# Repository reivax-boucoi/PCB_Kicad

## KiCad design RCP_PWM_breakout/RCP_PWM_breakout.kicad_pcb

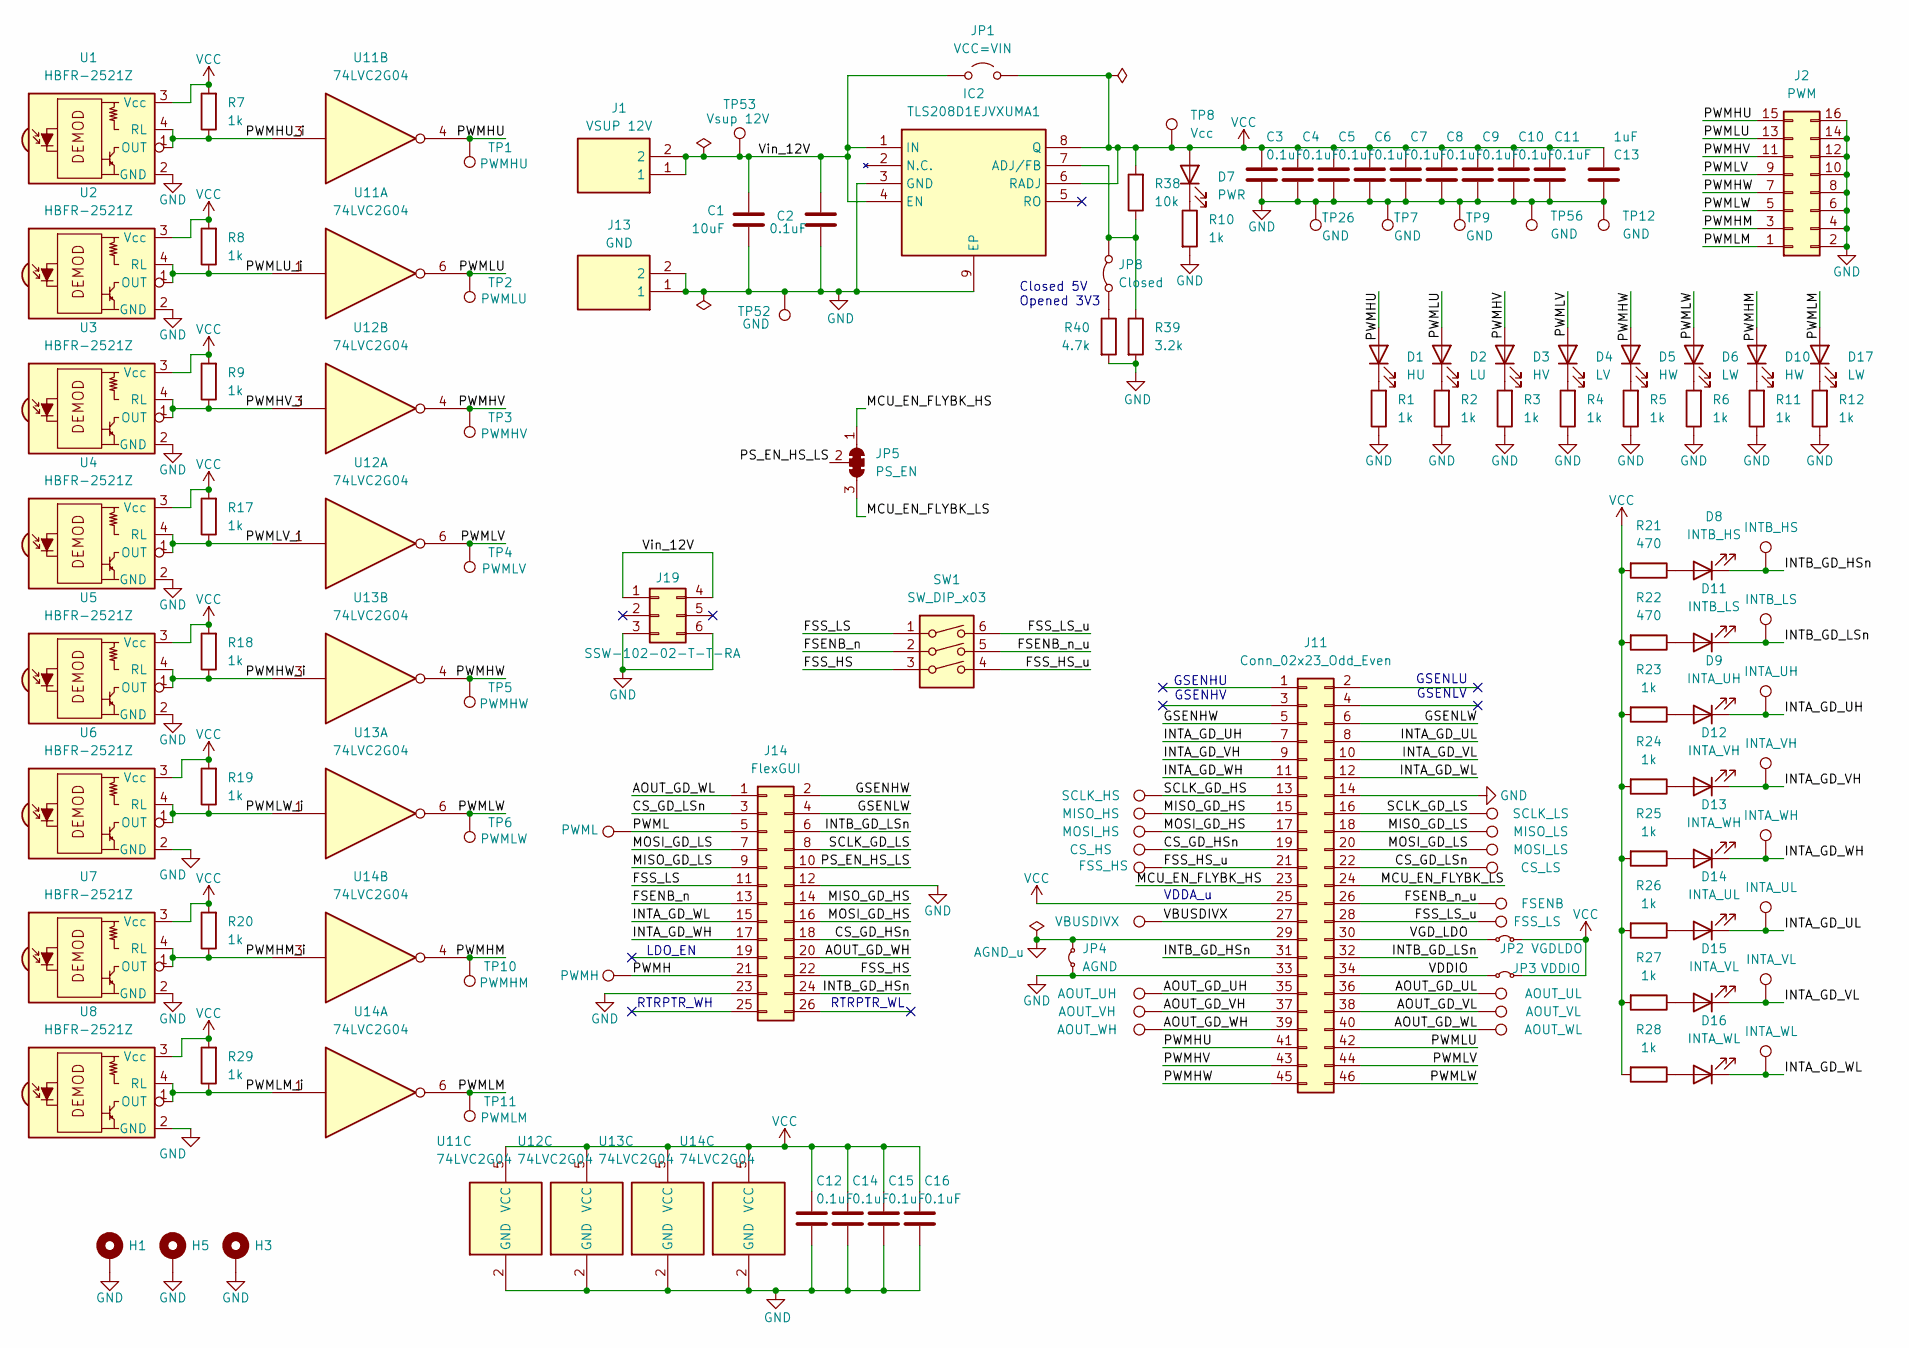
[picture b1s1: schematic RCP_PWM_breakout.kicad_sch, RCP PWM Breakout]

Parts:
C1: 10uF; C_0805_2012Metric_Pad1.18x1.45mm_HandSolder; MFG_PN 08053D106KAT2A; Mouser Part Number 581-08053D106KAT2A
C2, C3, C4, C5, C6, C7, C8, C9, C10, C11, C12, C14, C15, C16: 0.1uF; C_0603_1608Metric_Pad1.08x0.95mm_HandSolder; MFG_PN 06035C104JAT2A; Mouser Part Number 581-06035C104JAT2A
C13: 1uF; C_0805_2012Metric_Pad1.18x1.45mm_HandSolder; MFG_PN 08053D105KAT2A; Mouser Part Number 581-08053D105K
D1: HU; LED_0805_2012Metric; MFG_PN 598-8140-107F
D2: LU; LED_0805_2012Metric; MFG_PN 598-8140-107F
D3: HV; LED_0805_2012Metric; MFG_PN 598-8140-107F
D4: LV; LED_0805_2012Metric; MFG_PN 598-8140-107F
D5, D10: HW; LED_0805_2012Metric; MFG_PN 598-8140-107F
D6, D17: LW; LED_0805_2012Metric; MFG_PN 598-8140-107F
D7: PWR; LED_0805_2012Metric; MFG_PN 598-8181-107F
D8: INTB_HS; LED_0805_2012Metric; MFG_PN 598-8110-107F
D9: INTA_UH; LED_0805_2012Metric; MFG_PN 598-8130-107F
D11: INTB_LS; LED_0805_2012Metric; MFG_PN 598-8110-107F
D12: INTA_VH; LED_0805_2012Metric; MFG_PN 598-8130-107F
D13: INTA_WH; LED_0805_2012Metric; MFG_PN 598-8130-107F
D14: INTA_UL; LED_0805_2012Metric; MFG_PN 598-8130-107F
D15: INTA_VL; LED_0805_2012Metric; MFG_PN 598-8130-107F
D16: INTA_WL; LED_0805_2012Metric; MFG_PN 598-8130-107F
H1, H3, H5: MountingHole_Pad; MountingHole_3.2mm_M3_DIN965_Pad
IC2: TLS208D1EJVXUMA1; SOIC-8-1EP_3.9x4.9mm_P1.27mm_EP2.29x3mm_ThermalVias; Mouser Part Number 726-TLS208D1EJVXUMA1
J1: VSUP 12V; 1050752001; Mouser Part Number 530-105-0752-150
J2: PWM; PinHeader_2x08_P2.54mm_Vertical; MFG_PN TSW-103-07-S-D; Mouser Part Number 200-TSW10307SD
J11: Conn_02x23_Odd_Even; PinSocket_2x23_P2.54mm_Horizontal; MFG_PN SSW-123-02-T-D-RA; Mouser Part Number 200-SSW12302TDRA
J13: GND; 1050752001; Mouser Part Number 530-105-0753-150
J14: FlexGUI; PinHeader_2x13_P2.54mm_Vertical; MFG_PN TSW-113-07-S-D; Mouser Part Number 200-TSW11307SD
J19: SSW-102-02-T-T-RA; SAMTEC_SSW-102-02-T-T-RA; PARTREV R; Mouser Part Number 200-SSW10202TTRA
JP1: VCC=VIN; SolderJumper-2_P1.3mm_Open_RoundedPad1.0x1.5mm
JP2: VGDLDO; SolderJumper-2_P1.3mm_Bridged_RoundedPad1.0x1.5mm
JP3: VDDIO; SolderJumper-2_P1.3mm_Bridged_RoundedPad1.0x1.5mm
JP4: AGND; SolderJumper-2_P1.3mm_Bridged_RoundedPad1.0x1.5mm
JP5: PS_EN; SolderJumper-3_P1.3mm_Bridged123_Pad1.0x1.5mm_NumberLabels
JP8: Closed; SolderJumper-2P_Closed_THT+SMD
R1, R2, R3, R4, R5, R6, R7, R8, R9, R10, R11, R12, R17, R18, R19, R20, R23, R24, R25, R26, R27, R28, R29: 1k; R_0603_1608Metric_Pad0.98x0.95mm_HandSolder; MFG_PN CRCW06031K00FKEA; Mouser Part Number 71-CRCW0603-1.0K-E3
R21, R22: 470; R_0603_1608Metric_Pad0.98x0.95mm_HandSolder; MFG_PN CRCW0603470RFKEA; Mouser Part Number 71-CRCW0603-470-E3
R38: 10k; R_0603_1608Metric_Pad0.98x0.95mm_HandSolder; MFG_PN CRCW060310K0FKEA; Mouser Part Number 71-CRCW0603-10K-E3
R39: 3.2k; R_0603_1608Metric_Pad0.98x0.95mm_HandSolder; MFG_PN RN73H1JTTD3201F100; Mouser Part Number 660-RN73H1JT3201F100
R40: 4.7k; R_0603_1608Metric_Pad0.98x0.95mm_HandSolder; MFG_PN RK73H1JTTD4701F; Mouser Part Number 660-RK73H1JTTD4701F
SW1: SW_DIP_x03; SW_DIP_SPSTx03_Slide_6.7x9.18mm_W8.61mm_P2.54mm_LowProfile
TP1: PWMHU; TestPoint_Keystone_5012_white; MFG_PN 5012; Mouser PN 534-5012
TP2: PWMLU; TestPoint_Keystone_5012_white; MFG_PN 5012; Mouser PN 534-5012
TP3: PWMHV; TestPoint_Keystone_5012_white; MFG_PN 5012; Mouser PN 534-5012
TP4: PWMLV; TestPoint_Keystone_5012_white; MFG_PN 5012; Mouser PN 534-5012
TP5: PWMHW; TestPoint_Keystone_5012_white; MFG_PN 5012; Mouser PN 534-5012
TP6: PWMLW; TestPoint_Keystone_5012_white; MFG_PN 5012; Mouser PN 534-5012
TP7, TP9, TP26, TP52: GND; TestPoint_Keystone_5011_Black; MFG_PN 5011; Mouser PN 534-5011
TP8: Vcc; TestPoint_Keystone_5010_Red; MFG_PN 5010; Mouser PN 534-5012
TP10: PWMHM; TestPoint_Keystone_5012_white; MFG_PN 5012; Mouser PN 534-5012
TP11: PWMLM; TestPoint_Keystone_5012_white; MFG_PN 5012; Mouser PN 534-5012
TP12, TP56: GND; TestPoint_Keystone_5011_Black; MFG_PN 5011; Mouser PN 534-5012
TP18: MISO_HS; TestPoint_Keystone_5012_white; MFG_PN 5012; Mouser PN 534-5012
TP19: MOSI_HS; TestPoint_Keystone_5012_white; MFG_PN 5012; Mouser PN 534-5012
TP20: MOSI_LS; TestPoint_Keystone_5012_white; MFG_PN 5012; Mouser PN 534-5012
TP21: INTB_HS; TestPoint_Keystone_5012_white; MFG_PN 5012; Mouser PN 534-5012
TP22: AOUT_UH; TestPoint_Keystone_5012_white; MFG_PN 5012; Mouser PN 534-5012
TP23: AOUT_VH; TestPoint_Keystone_5012_white; MFG_PN 5012; Mouser PN 534-5012
TP24: AOUT_WH; TestPoint_Keystone_5012_white; MFG_PN 5012; Mouser PN 534-5012
TP25: CS_LS; TestPoint_Keystone_5012_white; MFG_PN 5012; Mouser PN 534-5012
TP27: PWMH; TestPoint_Keystone_5012_white; MFG_PN 5012; Mouser PN 534-5012
TP28: AOUT_UL; TestPoint_Keystone_5012_white; MFG_PN 5012; Mouser PN 534-5012
TP29: AOUT_VL; TestPoint_Keystone_5012_white; MFG_PN 5012; Mouser PN 534-5012
TP30: AOUT_WL; TestPoint_Keystone_5012_white; MFG_PN 5012; Mouser PN 534-5012
TP31: SCLK_HS; TestPoint_Keystone_5012_white; MFG_PN 5012; Mouser PN 534-5012
TP32: FSS_LS; TestPoint_Keystone_5012_white; MFG_PN 5012; Mouser PN 534-5012
TP33: FSENB; TestPoint_Keystone_5012_white; MFG_PN 5012; Mouser PN 534-5012
TP34: INTB_LS; TestPoint_Keystone_5012_white; MFG_PN 5012; Mouser PN 534-5012
TP35: INTA_UH; TestPoint_Keystone_5012_white; MFG_PN 5012; Mouser PN 534-5012
TP36: INTA_VH; TestPoint_Keystone_5012_white; MFG_PN 5012; Mouser PN 534-5012
TP37: INTA_WH; TestPoint_Keystone_5012_white; MFG_PN 5012; Mouser PN 534-5012
TP38: INTA_UL; TestPoint_Keystone_5012_white; MFG_PN 5012; Mouser PN 534-5012
TP39: INTA_VL; TestPoint_Keystone_5012_white; MFG_PN 5012; Mouser PN 534-5012
TP40: INTA_WL; TestPoint_Keystone_5012_white; MFG_PN 5012; Mouser PN 534-5012
TP41: FSS_HS; TestPoint_Keystone_5012_white; MFG_PN 5012; Mouser PN 534-5012
TP42: SCLK_LS; TestPoint_Keystone_5012_white; MFG_PN 5012; Mouser PN 534-5012
TP53: Vsup 12V; TestPoint_Keystone_5010_Red; MFG_PN 5010; Mouser PN 534-5012
TP54: PWML; TestPoint_Keystone_5012_white; MFG_PN 5012; Mouser PN 534-5012
TP60: CS_HS; TestPoint_Keystone_5012_white; MFG_PN 5012; Mouser PN 534-5012
TP61: MISO_LS; TestPoint_Keystone_5012_white; MFG_PN 5012; Mouser PN 534-5012
TP62: VBUSDIVX; TestPoint_Keystone_5012_white; MFG_PN 5012; Mouser PN 534-5012
U1, U2, U3, U4, U5, U6, U7, U8: HBFR-2521Z; FR50MHNR
U11, U12, U13, U14: 74LVC2G04; SOT-23-6_Handsoldering

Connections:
/AOUT_GD_UH: J11.35, TP22.1 (1_1)
/AOUT_GD_UL: J11.36, TP28.1 (1_1)
/AOUT_GD_VH: J11.37, TP23.1 (1_1)
/AOUT_GD_VL: J11.38, TP29.1 (1_1)
/AOUT_GD_WH: J11.39, J14.20, TP24.1 (1_1)
/AOUT_GD_WL: J11.40, J14.1, TP30.1 (1_1)
/CS_GD_HSn: J11.19, J14.18, TP60.1 (1_1)
/CS_GD_LSn: J11.22, J14.3, TP25.1 (1_1)
/FSENB_n: J14.13, SW1.2
/FSENB_n_u: J11.26, SW1.5, TP33.1 (1_1)
/FSS_HS: J14.22, SW1.3
/FSS_HS_u: J11.21, SW1.4, TP41.1 (1_1)
/FSS_LS: J14.11, SW1.1
/FSS_LS_u: J11.28, SW1.6, TP32.1 (1_1)
/GSENHW: J11.5, J14.2
/GSENLW: J11.6, J14.4
/INTA_GD_UH: D9.1 (K), J11.7, TP35.1 (1_1)
/INTA_GD_UL: D14.1 (K), J11.8, TP38.1 (1_1)
/INTA_GD_VH: D12.1 (K), J11.9, TP36.1 (1_1)
/INTA_GD_VL: D15.1 (K), J11.10, TP39.1 (1_1)
/INTA_GD_WH: D13.1 (K), J11.11, J14.17, TP37.1 (1_1)
/INTA_GD_WL: D16.1 (K), J11.12, J14.15, TP40.1 (1_1)
/INTB_GD_HSn: D8.1 (K), J11.31, J14.24, TP21.1 (1_1)
/INTB_GD_LSn: D11.1 (K), J11.32, J14.6, TP34.1 (1_1)
/MCU_EN_FLYBK_HS: J11.23, JP5.1 (A)
/MCU_EN_FLYBK_LS: J11.24, JP5.3 (B)
/MISO_GD_HS: J11.15, J14.14, TP18.1 (1_1)
/MISO_GD_LS: J11.18, J14.9, TP61.1 (1_1)
/MOSI_GD_HS: J11.17, J14.16, TP19.1 (1_1)
/MOSI_GD_LS: J11.20, J14.7, TP20.1 (1_1)
/PS_EN_HS_LS: J14.10, JP5.2 (C)
/PWMH: J14.21, TP27.1 (1_1)
/PWMHM: D10.2 (A), J2.3, TP10.1 (1_1), U14.4
/PWMHM_i: R20.1, U7.1 (OUT), U7.4 (RL), U14.3
/PWMHU: D1.2 (A), J2.15, J11.41, TP1.1 (1_1), U11.4
/PWMHU_i: R7.1, U1.1 (OUT), U1.4 (RL), U11.3
/PWMHV: D3.2 (A), J2.11, J11.43, TP3.1 (1_1), U12.4
/PWMHV_i: R9.1, U3.1 (OUT), U3.4 (RL), U12.3
/PWMHW: D5.2 (A), J2.7, J11.45, TP5.1 (1_1), U13.4
/PWMHW_i: R18.1, U5.1 (OUT), U5.4 (RL), U13.3
/PWML: J14.5, TP54.1 (1_1)
/PWMLM: D17.2 (A), J2.1, TP11.1 (1_1), U14.6
/PWMLM_i: R29.1, U8.1 (OUT), U8.4 (RL), U14.1
/PWMLU: D2.2 (A), J2.13, J11.42, TP2.1 (1_1), U11.6
/PWMLU_i: R8.1, U2.1 (OUT), U2.4 (RL), U11.1
/PWMLV: D4.2 (A), J2.9, J11.44, TP4.1 (1_1), U12.6
/PWMLV_i: R17.1, U4.1 (OUT), U4.4 (RL), U12.1
/PWMLW: D6.2 (A), J2.5, J11.46, TP6.1 (1_1), U13.6
/PWMLW_i: R19.1, U6.1 (OUT), U6.4 (RL), U13.1
/SCLK_GD_HS: J11.13, TP31.1 (1_1)
/SCLK_GD_LS: J11.16, J14.8, TP42.1 (1_1)
/VBUSDIVX: J11.27, TP62.1 (1_1)
/VDDIO: J11.34, JP3.1 (A)
/VGD_LDO: J11.30, JP2.1 (A)
/Vin_12V: C1.1, C2.2, IC2.1 (IN), IC2.4 (EN), J1.1, J1.2, J19.1, J19.4, JP1.1 (A), TP53.1 (1_1)
AGND_u: J11.29, JP4.2 (B)
GND: C1.2, C2.1, C3.2, C4.2, C5.2, C6.2, C7.2, C8.2, C9.2, C10.2, C11.2, C12.2, C13.1, C14.2, C15.2, C16.2, H1.1 (1_1), H3.1 (1_1), H5.1 (1_1), IC2.3 (GND), IC2.9 (EP), J2.2, J2.4, J2.6, J2.8, J2.10, J2.12, J2.14, J2.16, J11.14, J11.33, J13.1, J13.2, J14.12, J14.23, J19.3, J19.6, JP4.1 (A), R1.1, R2.1, R3.1, R4.1, R5.1, R6.1, R10.2, R11.1, R12.1, R39.2, R40.2, TP7.1 (1_1), TP9.1 (1_1), TP12.1 (1_1), TP26.1 (1_1), TP52.1 (1_1), TP56.1 (1_1), U1.2 (GND), U1.5 (GND), U1.8 (GND), U2.2 (GND), U2.5 (GND), U2.8 (GND), U3.2 (GND), U3.5 (GND), U3.8 (GND), U4.2 (GND), U4.5 (GND), U4.8 (GND), U5.2 (GND), U5.5 (GND), U5.8 (GND), U6.2 (GND), U6.5 (GND), U6.8 (GND), U7.2 (GND), U7.5 (GND), U7.8 (GND), U8.2 (GND), U8.5 (GND), U8.8 (GND), U11.2 (GND), U12.2 (GND), U13.2 (GND), U14.2 (GND)
unnamed: D1.1 (K), R1.2
unnamed: D2.1 (K), R2.2
unnamed: D3.1 (K), R3.2
unnamed: D4.1 (K), R4.2
unnamed: D5.1 (K), R5.2
unnamed: D6.1 (K), R6.2
unnamed: D7.1 (K), R10.1
unnamed: D8.2 (A), R21.1
unnamed: D9.2 (A), R23.1
unnamed: D10.1 (K), R11.2
unnamed: D11.2 (A), R22.1
unnamed: D12.2 (A), R24.1
unnamed: D13.2 (A), R25.1
unnamed: D14.2 (A), R26.1
unnamed: D15.2 (A), R27.1
unnamed: D16.2 (A), R28.1
unnamed: D17.1 (K), R12.2
unnamed: IC2.7 (ADJ/FB), JP8.2 (B), R38.1, R39.1
unnamed: JP8.1 (A), R40.1
VCC: C3.1, C4.1, C5.1, C6.1, C7.1, C8.1, C9.1, C10.1, C11.1, C12.1, C13.2, C14.1, C15.1, C16.1, D7.2 (A), IC2.6 (RADJ), IC2.8 (Q), J11.25, JP1.2 (B), JP2.2 (B), JP3.2 (B), R7.2, R8.2, R9.2, R17.2, R18.2, R19.2, R20.2, R21.2, R22.2, R23.2, R24.2, R25.2, R26.2, R27.2, R28.2, R29.2, R38.2, TP8.1 (1_1), U1.3 (Vcc), U2.3 (Vcc), U3.3 (Vcc), U4.3 (Vcc), U5.3 (Vcc), U6.3 (Vcc), U7.3 (Vcc), U8.3 (Vcc), U11.5 (VCC), U12.5 (VCC), U13.5 (VCC), U14.5 (VCC)

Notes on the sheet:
RTRPTR_WH
LDO_EN
RTRPTR_WL
VDDA_u
GSENLU GSENLV
Closed 5V Opened 3V3
GSENHU GSENHV

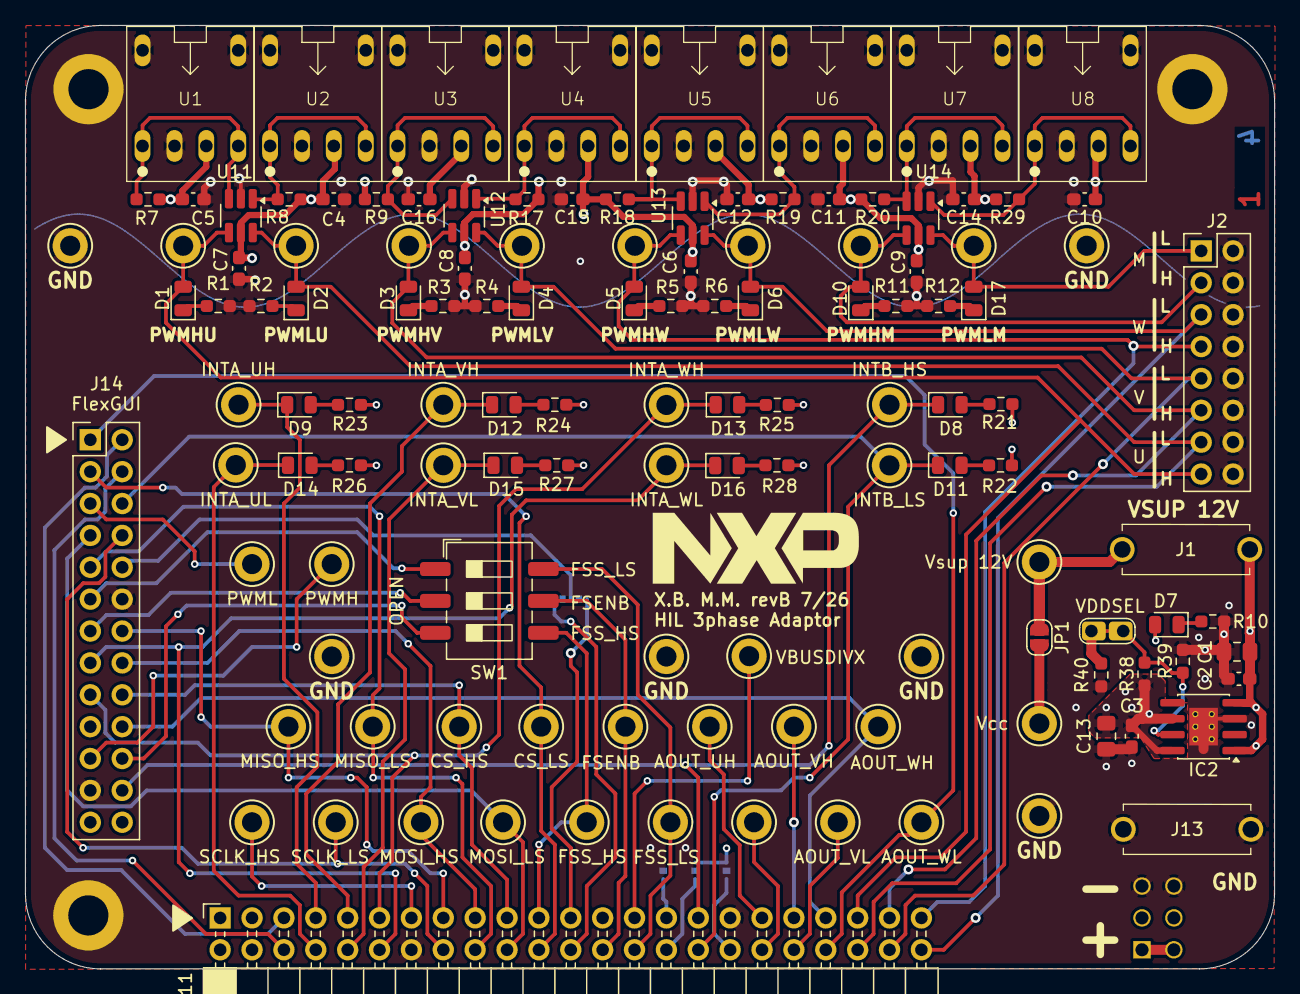
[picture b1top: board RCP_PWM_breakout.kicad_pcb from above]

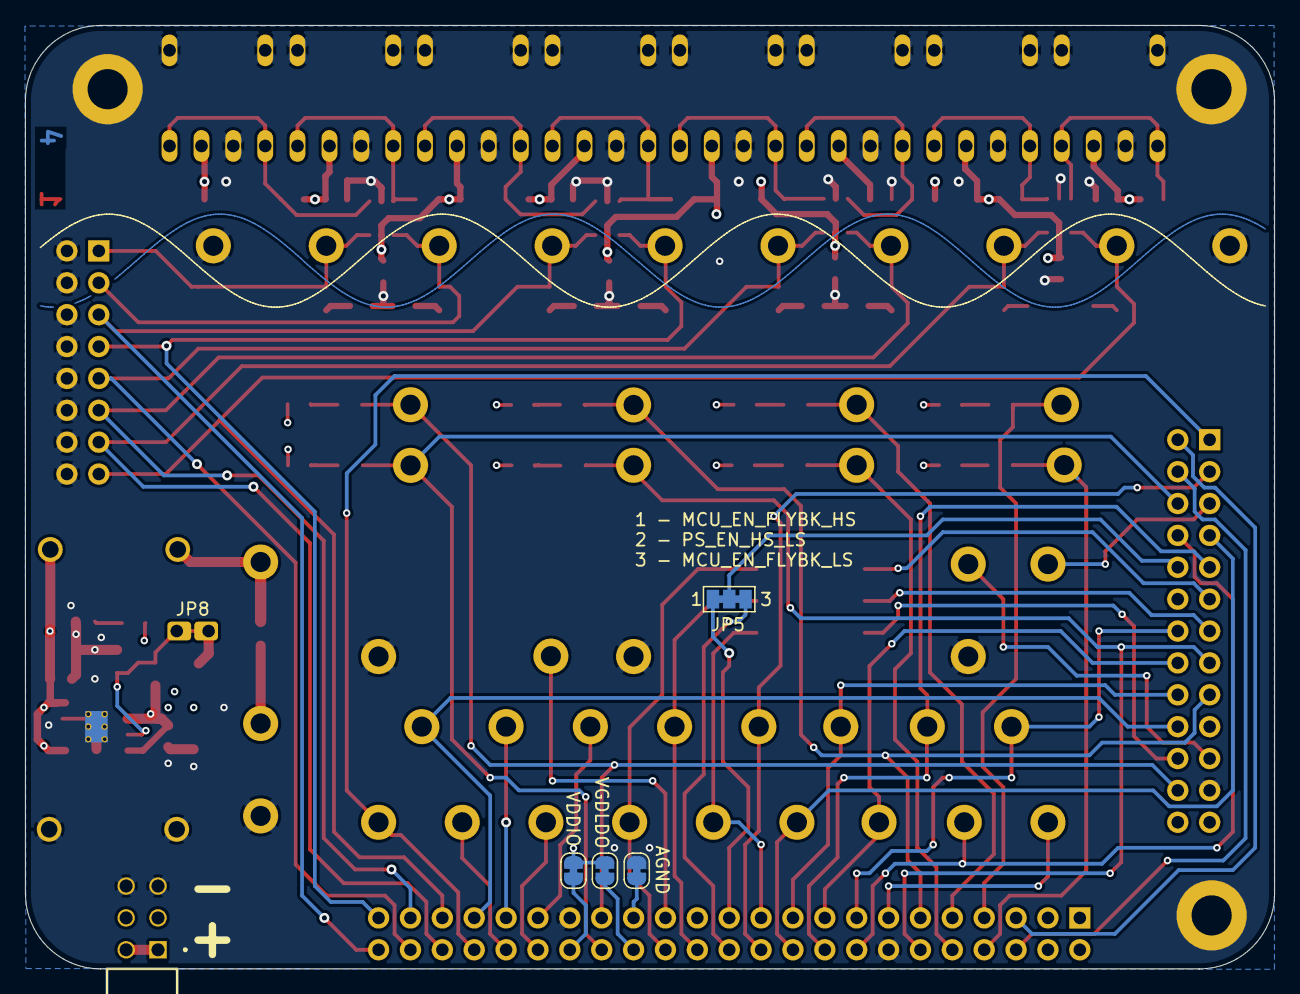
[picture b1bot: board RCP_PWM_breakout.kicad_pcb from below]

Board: 4 copper layers, 99.5 x 75.2 mm, 134 parts (5 on the bottom side), 77 nets.

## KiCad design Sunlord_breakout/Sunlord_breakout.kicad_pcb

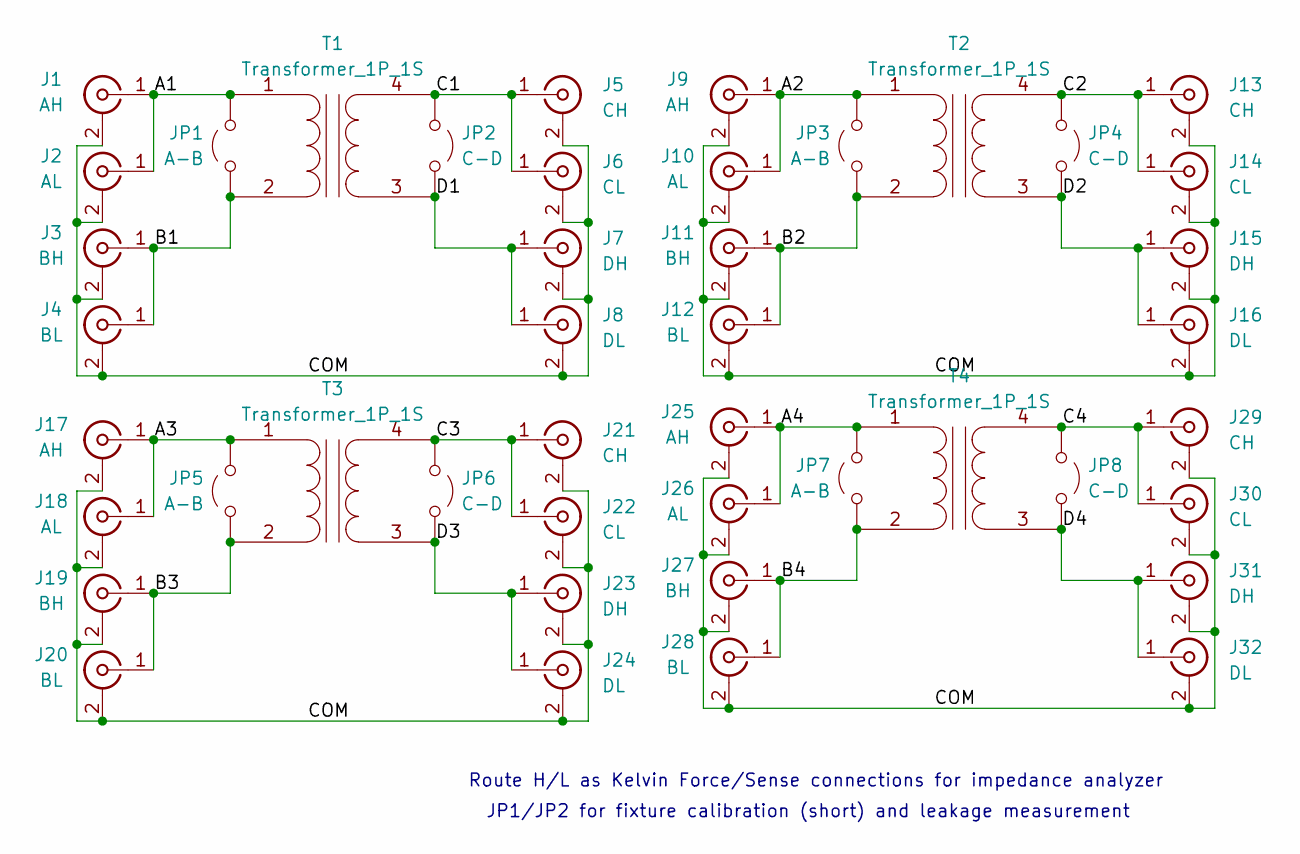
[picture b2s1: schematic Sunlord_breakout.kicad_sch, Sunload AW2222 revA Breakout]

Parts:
J1, J9, J17, J25: AH; SMA_Samtec_SMA-J-P-H-ST-EM1_EdgeMount
J2, J10, J18, J26: AL; SMA_Samtec_SMA-J-P-H-ST-EM1_EdgeMount
J3, J11, J19, J27: BH; SMA_Samtec_SMA-J-P-H-ST-EM1_EdgeMount
J4, J12, J20, J28: BL; SMA_Samtec_SMA-J-P-H-ST-EM1_EdgeMount
J5, J13, J21, J29: CH; SMA_Samtec_SMA-J-P-H-ST-EM1_EdgeMount
J6, J14, J22, J30: CL; SMA_Samtec_SMA-J-P-H-ST-EM1_EdgeMount
J7, J15, J23, J31: DH; SMA_Samtec_SMA-J-P-H-ST-EM1_EdgeMount
J8, J16, J24, J32: DL; SMA_Samtec_SMA-J-P-H-ST-EM1_EdgeMount
JP1, JP3, JP5, JP7: A-B; SolderJumper-2_P1.3mm_Open_RoundedPad1.0x1.5mm
JP2, JP4, JP6, JP8: C-D; SolderJumper-2_P1.3mm_Open_RoundedPad1.0x1.5mm
T1, T2, T3, T4: Transformer_1P_1S; AW2222_Sunlord_µXFMR

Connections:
/A1: J1.1 (In), J2.1 (In), JP1.2 (B), T1.1 (AA)
/A2: J9.1 (In), J10.1 (In), JP3.2 (B), T2.1 (AA)
/A3: J17.1 (In), J18.1 (In), JP5.2 (B), T3.1 (AA)
/A4: J25.1 (In), J26.1 (In), JP7.2 (B), T4.1 (AA)
/B1: J3.1 (In), J4.1 (In), JP1.1 (A), T1.2 (AB)
/B2: J11.1 (In), J12.1 (In), JP3.1 (A), T2.2 (AB)
/B3: J19.1 (In), J20.1 (In), JP5.1 (A), T3.2 (AB)
/B4: J27.1 (In), J28.1 (In), JP7.1 (A), T4.2 (AB)
/C1: J5.1 (In), J6.1 (In), JP2.1 (A), T1.4 (SB)
/C2: J13.1 (In), J14.1 (In), JP4.1 (A), T2.4 (SB)
/C3: J21.1 (In), J22.1 (In), JP6.1 (A), T3.4 (SB)
/C4: J29.1 (In), J30.1 (In), JP8.1 (A), T4.4 (SB)
/COM: J1.2 (Ext), J2.2 (Ext), J3.2 (Ext), J4.2 (Ext), J5.2 (Ext), J6.2 (Ext), J7.2 (Ext), J8.2 (Ext), J9.2 (Ext), J10.2 (Ext), J11.2 (Ext), J12.2 (Ext), J13.2 (Ext), J14.2 (Ext), J15.2 (Ext), J16.2 (Ext), J17.2 (Ext), J18.2 (Ext), J19.2 (Ext), J20.2 (Ext), J21.2 (Ext), J22.2 (Ext), J23.2 (Ext), J24.2 (Ext), J25.2 (Ext), J26.2 (Ext), J27.2 (Ext), J28.2 (Ext), J29.2 (Ext), J30.2 (Ext), J31.2 (Ext), J32.2 (Ext)
/D1: J7.1 (In), J8.1 (In), JP2.2 (B), T1.3 (SA)
/D2: J15.1 (In), J16.1 (In), JP4.2 (B), T2.3 (SA)
/D3: J23.1 (In), J24.1 (In), JP6.2 (B), T3.3 (SA)
/D4: J31.1 (In), J32.1 (In), JP8.2 (B), T4.3 (SA)

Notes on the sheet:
JP1/JP2 for fixture calibration (short) and leakage measurement
Route H/L as Kelvin Force/Sense connections for impedance analyzer

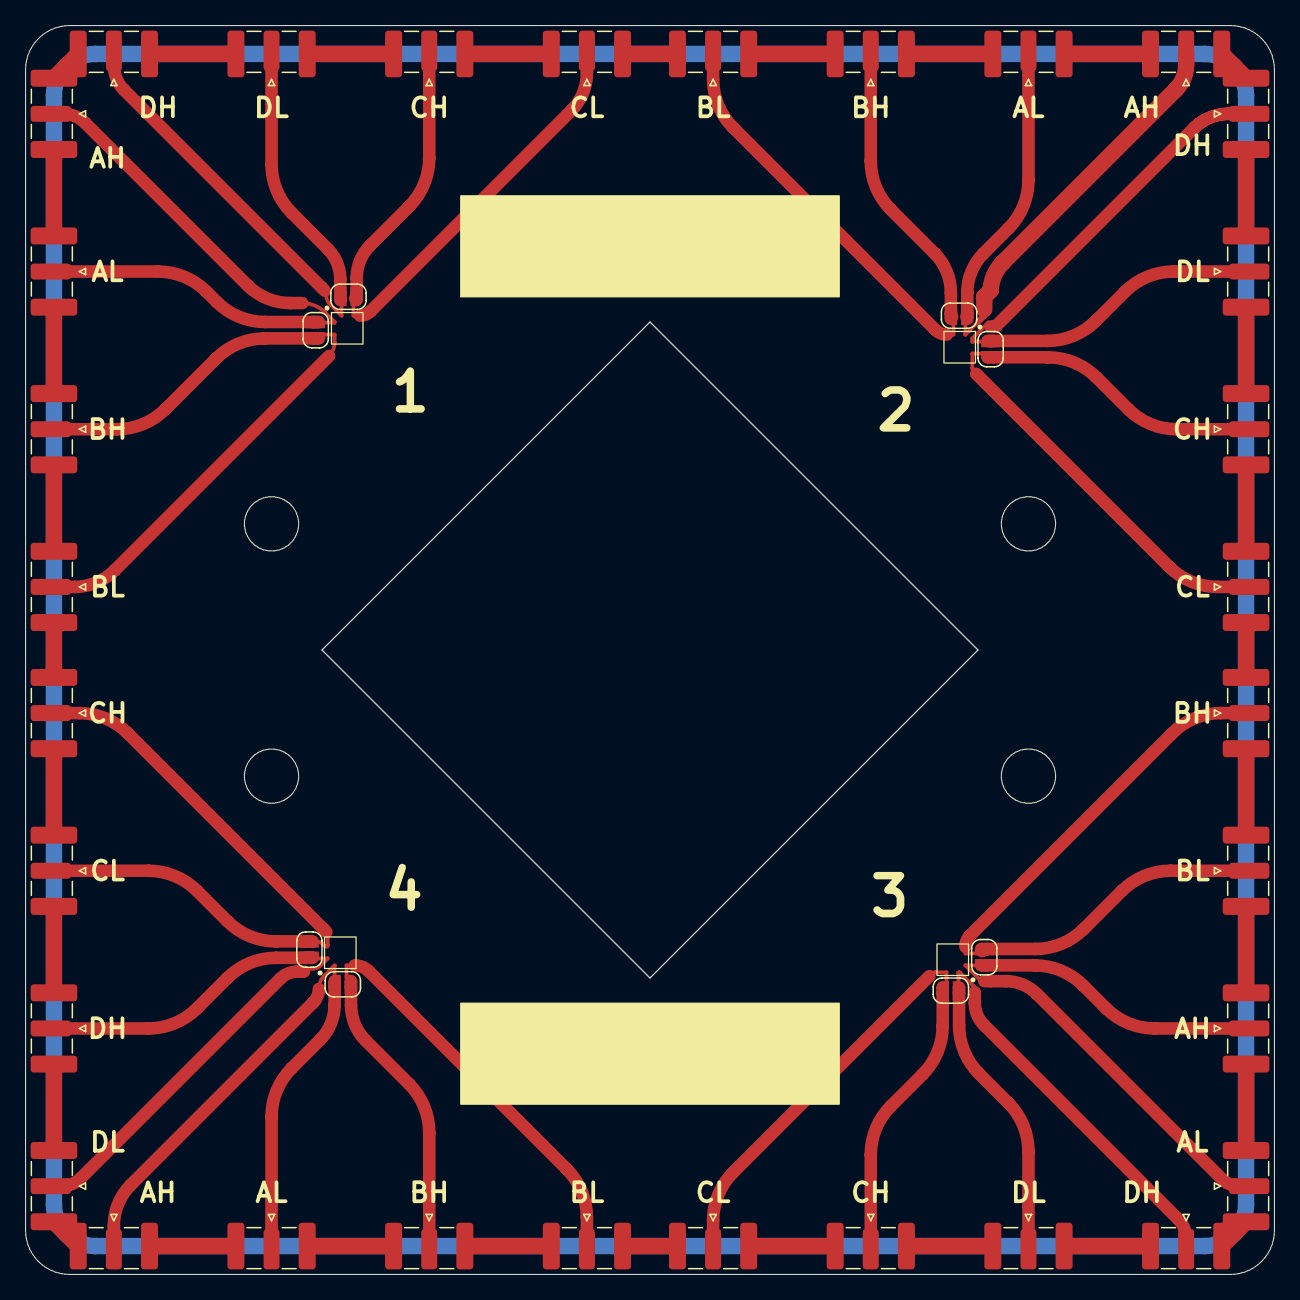
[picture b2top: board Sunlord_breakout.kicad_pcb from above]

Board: 2 copper layers, 99.0 x 99.0 mm, 44 parts (0 on the bottom side), 17 nets.

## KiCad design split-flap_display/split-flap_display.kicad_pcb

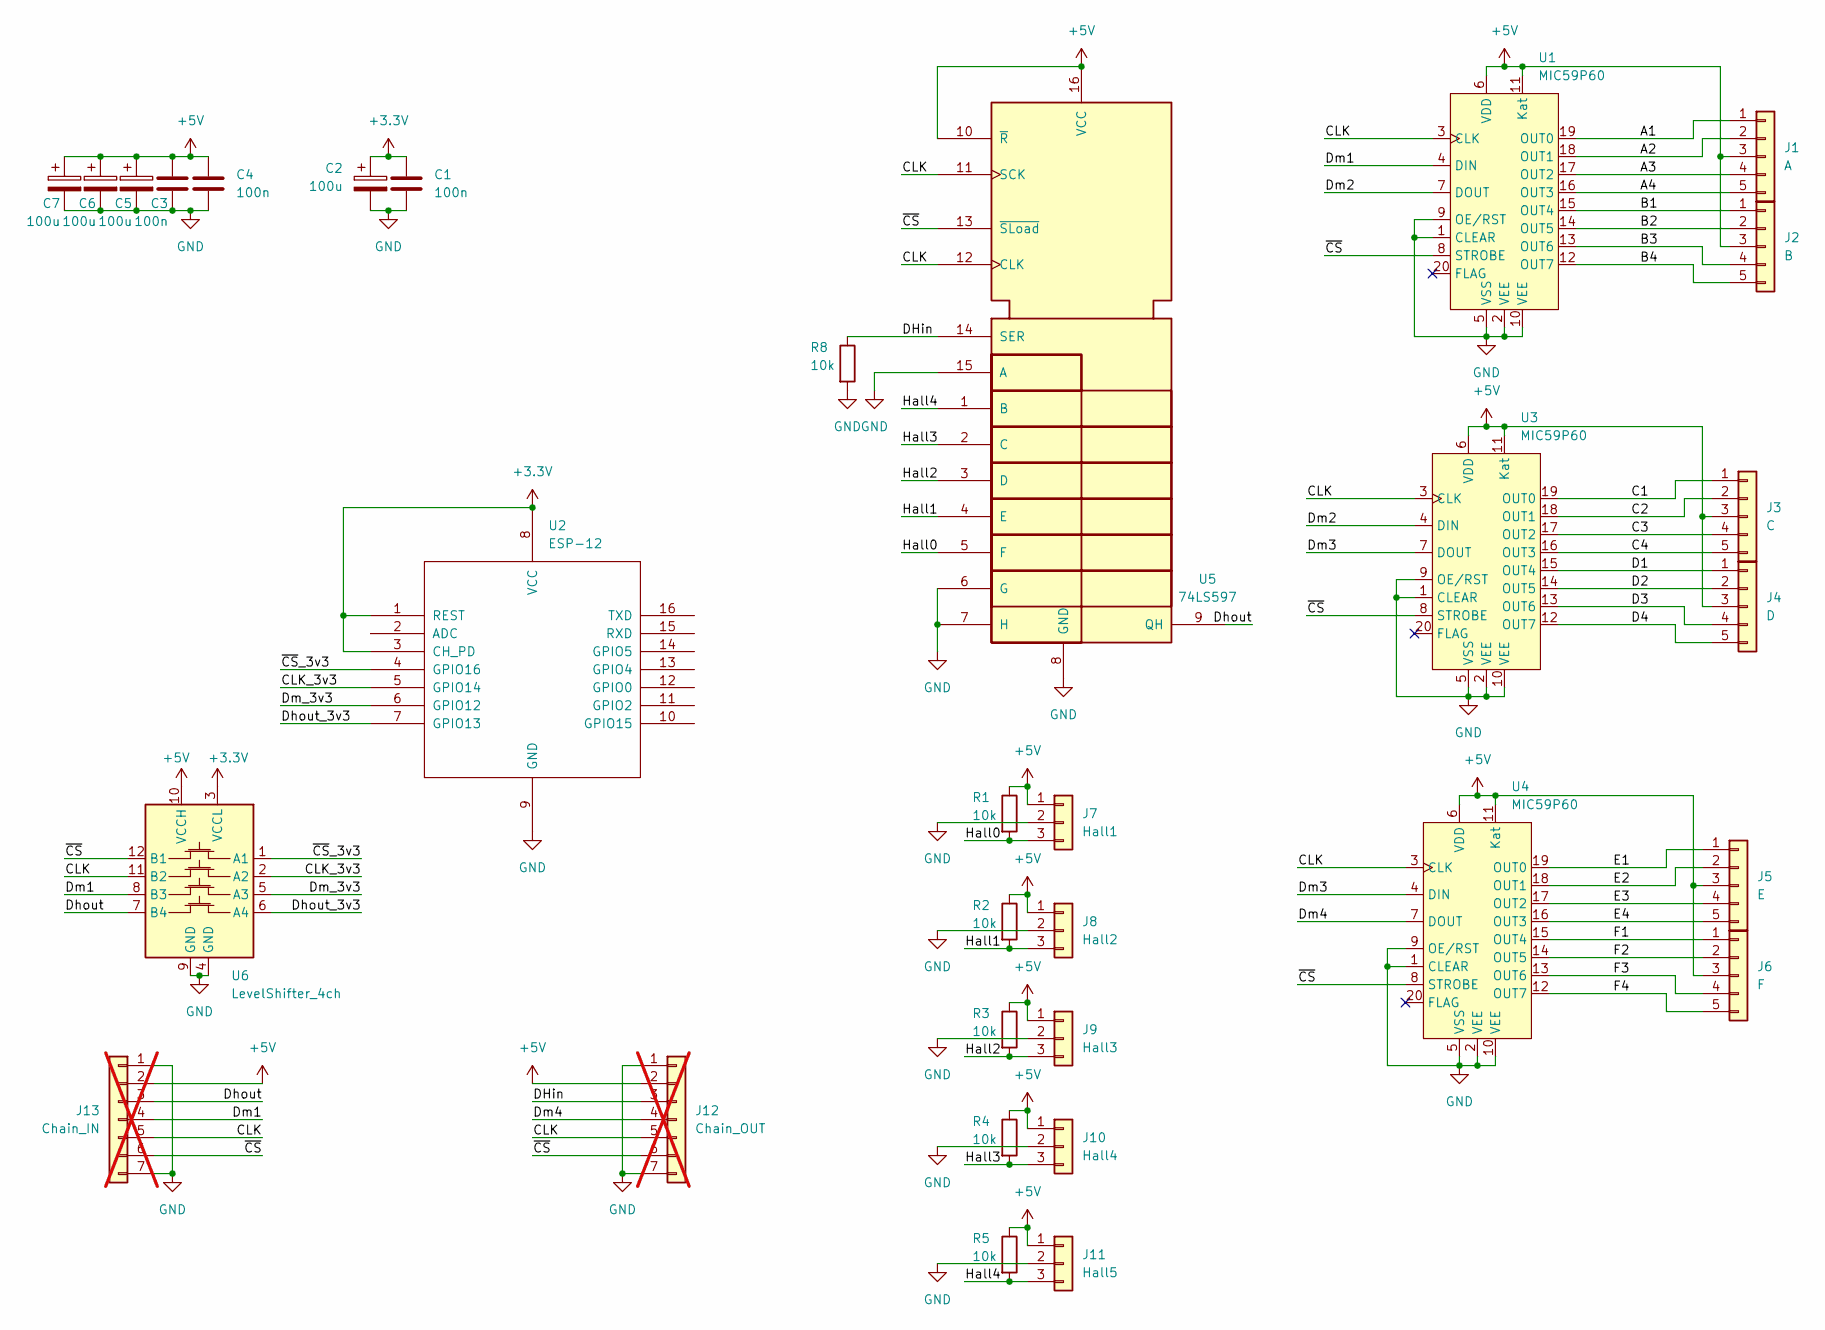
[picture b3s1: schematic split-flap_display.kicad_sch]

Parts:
C1, C3, C4: 100n; C_Disc_D6.0mm_W2.5mm_P5.00mm
C2, C5, C6, C7: 100u; CP_Radial_D8.0mm_P5.00mm
J1: A; PinHeader_1x05_P2.54mm_Vertical
J2: B; PinHeader_1x05_P2.54mm_Vertical
J3: C; PinHeader_1x05_P2.54mm_Vertical
J4: D; PinHeader_1x05_P2.54mm_Vertical
J5: E; PinHeader_1x05_P2.54mm_Vertical
J6: F; PinHeader_1x05_P2.54mm_Vertical
J7: Hall1; PinHeader_1x03_P2.54mm_Vertical
J8: Hall2; PinHeader_1x03_P2.54mm_Vertical
J9: Hall3; PinHeader_1x03_P2.54mm_Vertical
J10: Hall4; PinHeader_1x03_P2.54mm_Vertical
J11: Hall5; PinHeader_1x03_P2.54mm_Vertical
J12: Chain_OUT; PinHeader_1x07_P2.54mm_Vertical; not fitted
J13: Chain_IN; PinHeader_1x07_P2.54mm_Vertical; not fitted
R1, R2, R3, R4, R5: 10k; R_Axial_DIN0207_L6.3mm_D2.5mm_P5.08mm_Vertical
R8: 10k; R_Axial_DIN0207_L6.3mm_D2.5mm_P2.54mm_Vertical
U1, U3, U4: MIC59P60; DIP-20_W7.62mm_LongPads
U2: ESP-12
U5: 74LS597; DIP-16_W7.62mm_LongPads
U6: LevelShifter_4ch; DIP-12_LevelShifter

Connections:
+3.3V: C1.1, C2.1, U2.1 (REST), U2.3 (CH_PD), U2.8 (VCC), U6.3 (VCCL)
+5V: C3.1, C4.1, C5.1, C6.1, C7.1, J1.3, J2.3, J3.3, J4.3, J5.3, J6.3, J7.1, J8.1, J9.1, J10.1, J11.1, J12.2, J13.2, R1.1, R2.1, R3.1, R4.1, R5.1, U1.6 (VDD), U1.11 (Kat), U3.6 (VDD), U3.11 (Kat), U4.6 (VDD), U4.11 (Kat), U5.10 (~R), U5.16 (VCC), U6.10 (VCCH)
/A1: J1.1, U1.19 (OUT0)
/A2: J1.2, U1.18 (OUT1)
/A3: J1.4, U1.17 (OUT2)
/A4: J1.5, U1.16 (OUT3)
/B1: J2.1, U1.15 (OUT4)
/B2: J2.2, U1.14 (OUT5)
/B3: J2.4, U1.13 (OUT6)
/B4: J2.5, U1.12 (OUT7)
/C1: J3.1, U3.19 (OUT0)
/C2: J3.2, U3.18 (OUT1)
/C3: J3.4, U3.17 (OUT2)
/C4: J3.5, U3.16 (OUT3)
/CLK: J12.5, J13.5, U1.3 (CLK), U3.3 (CLK), U4.3 (CLK), U5.11 (SCK), U5.12 (CLK), U6.11 (B2)
/CLK_3v3: U2.5 (GPIO14), U6.2 (A2)
/D1: J4.1, U3.15 (OUT4)
/D2: J4.2, U3.14 (OUT5)
/D3: J4.4, U3.13 (OUT6)
/D4: J4.5, U3.12 (OUT7)
/DHin: J12.3, R8.1, U5.14 (SER)
/Dhout: J13.3, U5.9 (QH), U6.7 (B4)
/Dhout_3v3: U2.7 (GPIO13), U6.6 (A4)
/Dm1: J13.4, U1.4 (DIN), U6.8 (B3)
/Dm2: U1.7 (DOUT), U3.4 (DIN)
/Dm3: U3.7 (DOUT), U4.4 (DIN)
/Dm4: J12.4, U4.7 (DOUT)
/Dm_3v3: U2.6 (GPIO12), U6.5 (A3)
/E1: J5.1, U4.19 (OUT0)
/E2: J5.2, U4.18 (OUT1)
/E3: J5.4, U4.17 (OUT2)
/E4: J5.5, U4.16 (OUT3)
/F1: J6.1, U4.15 (OUT4)
/F2: J6.2, U4.14 (OUT5)
/F3: J6.4, U4.13 (OUT6)
/F4: J6.5, U4.12 (OUT7)
/Hall0: J7.3, R1.2, U5.5 (F)
/Hall1: J8.3, R2.2, U5.4 (E)
/Hall2: J9.3, R3.2, U5.3 (D)
/Hall3: J10.3, R4.2, U5.2 (C)
/Hall4: J11.3, R5.2, U5.1 (B)
/~CS: J12.6, J13.6, U1.8 (STROBE), U3.8 (STROBE), U4.8 (STROBE), U5.13 (~SLoad), U6.12 (B1)
/~CS_3v3: U2.4 (GPIO16), U6.1 (A1)
GND: C1.2, C2.2, C3.2, C4.2, C5.2, C6.2, C7.2, J7.2, J8.2, J9.2, J10.2, J11.2, J12.1, J12.7, J13.1, J13.7, R8.2, U1.1 (CLEAR), U1.2 (VEE), U1.5 (VSS), U1.9 (OE/RST), U1.10 (VEE), U2.9 (GND), U3.1 (CLEAR), U3.2 (VEE), U3.5 (VSS), U3.9 (OE/RST), U3.10 (VEE), U4.1 (CLEAR), U4.2 (VEE), U4.5 (VSS), U4.9 (OE/RST), U4.10 (VEE), U5.6 (G), U5.7 (H), U5.8 (GND), U5.15 (A), U6.4 (GND), U6.9 (GND)

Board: 2 copper layers, 30 parts (5 on the bottom side), 43 nets, no tracks yet.

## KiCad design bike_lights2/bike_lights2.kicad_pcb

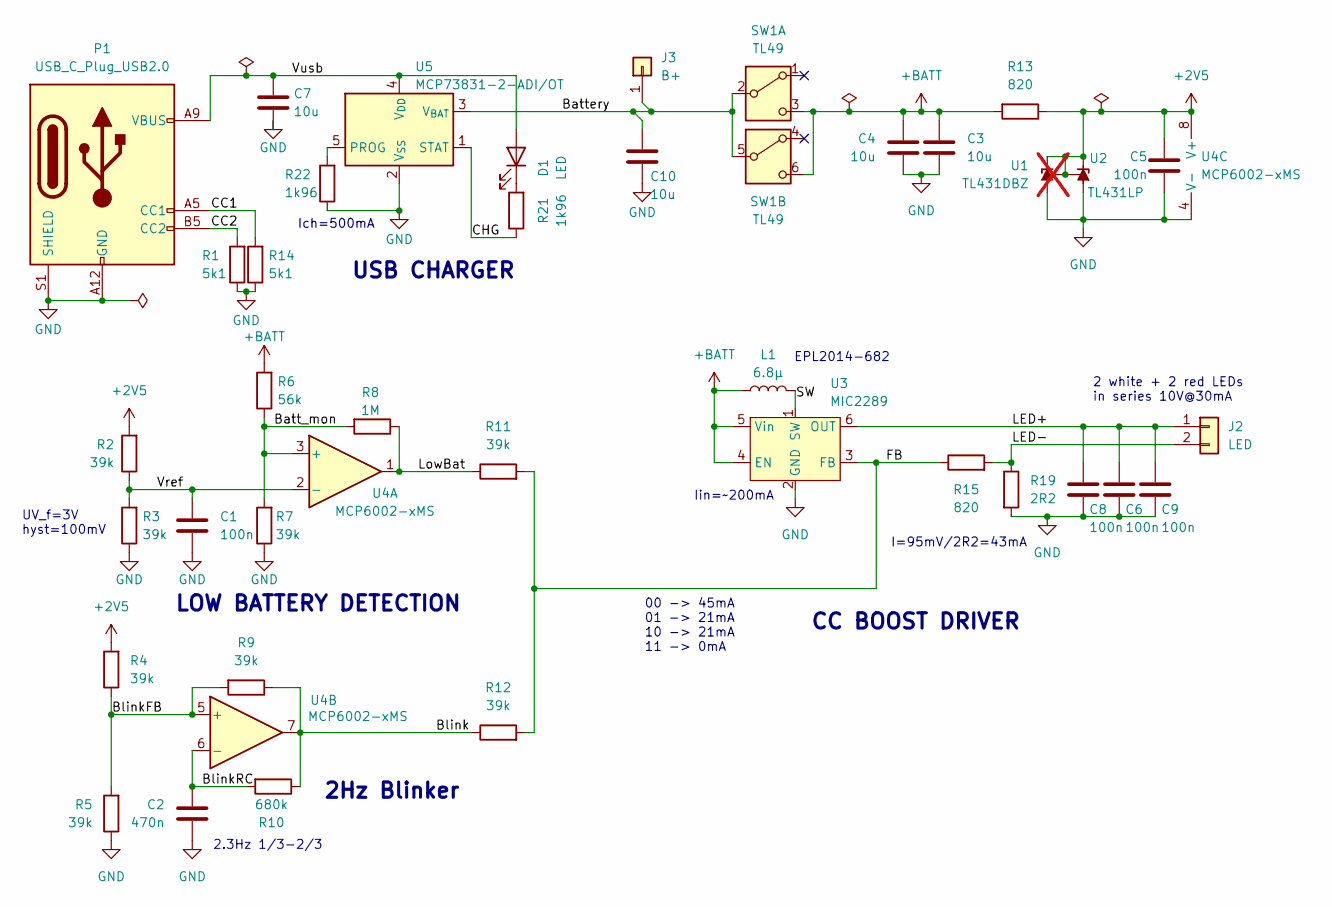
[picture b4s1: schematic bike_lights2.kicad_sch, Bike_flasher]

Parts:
C1, C5, C6, C8, C9: 100n; C_0402_1005Metric
C2: 470n; C_0603_1608Metric
C3, C4, C7, C10: 10u; C_0603_1608Metric
D1: LED; LED_0603_1608Metric
J2: LED; JST_PH_1x02_P2.0-2.5mm_Vertical
J3: B+; SolderWire-0.5sqmm_1x01_D0.9mm_OD2.1mm
L1: 6.8µ; EPL2014_2x2mm_inductor_Coilcraft
P1: USB_C_Plug_USB2.0; USB_C_Receptacle_GCT_USB4125-xx-x_6P_TopMnt_Horizontal
R1, R14: 5k1; R_0603_1608Metric
R2, R3, R4, R5, R7, R9, R11, R12: 39k; R_0603_1608Metric
R6: 56k; R_0603_1608Metric
R8: 1M; R_0603_1608Metric
R10: 680k; R_0603_1608Metric
R13, R15: 820; R_0603_1608Metric
R19: 2R2; R_0603_1608Metric
R21, R22: 1k96; R_0603_1608Metric
SW1: TL49; TL49PO
U1: TL431DBZ; SOT-23; not fitted
U2: TL431LP; TO-92_Inline
U3: MIC2289; SOT-23-6
U4: MCP6002-xMS; MSOP-8_3x3mm_P0.65mm
U5: MCP73831-2-ADI/OT; SOT-23-5

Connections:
+2V5: C5.1, R2.2, R4.2, R13.1, U1.1 (K), U1.2 (REF), U2.1 (REF), U2.3 (K), U4.8 (V+)
+BATT: C3.1, C4.1, L1.1, R6.2, R13.2, SW1.3 (C), SW1.6 (C), U3.4 (EN), U3.5 (Vin)
/Batt_mon: R6.1, R7.2, R8.2, U4.3 (+)
/Battery: C10.1, J3.1 (Pin_1_1), SW1.2 (B), SW1.5 (B), U5.3 (V_{BAT})
/Blink: R9.1, R10.1, R12.1, U4.7
/BlinkFB: R4.1, R5.2, R9.2, U4.5 (+)
/BlinkRC: C2.1, R10.2, U4.6 (-)
/CC1: P1.A5 (CC1), R14.2
/CC2: P1.B5 (CC2), R1.2
/CHG: R21.1, U5.1 (STAT)
/FB: R11.2, R12.2, R15.1, U3.3 (FB)
/LED+: C6.1, C8.1, C9.1, J2.1, U3.6 (OUT)
/LED-: J2.2, R15.2, R19.1
/LowBat: R8.1, R11.1, U4.1
/SW: L1.2, U3.1 (SW)
/Vref: C1.1, R2.1, R3.2, U4.2 (-)
/Vusb: C7.1, D1.2 (A), P1.A9 (VBUS), P1.B9 (VBUS), U5.4 (V_{DD})
GND: C1.2, C2.2, C3.2, C4.2, C5.2, C6.2, C7.2, C8.2, C9.2, C10.2, P1.A12 (GND), P1.B12 (GND), P1.S1 (SHIELD), R1.1, R3.1, R5.1, R7.1, R14.1, R19.2, R22.1, U1.3 (A), U2.2 (A), U3.2 (GND), U4.4 (V-), U5.2 (V_{SS})
unnamed: D1.1 (K), R21.2
unnamed: R22.2, U5.5 (PROG)

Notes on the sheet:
2.3Hz 1/3-2/3
2Hz Blinker
CC BOOST DRIVER
UV_f=3V hyst=100mV
00 -> 45mA 01 -> 21mA 10 -> 21mA 11 -> 0mA
Ich=500mA
2 white + 2 red LEDs in series 10V@30mA
EPL2014-682
LOW BATTERY DETECTION
I=95mV/2R2=43mA
Iin=~200mA
USB CHARGER

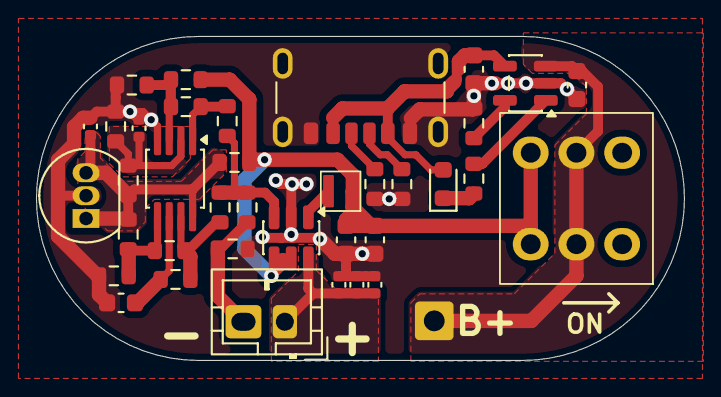
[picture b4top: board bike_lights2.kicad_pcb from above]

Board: 2 copper layers, 36.0 x 18.0 mm, 38 parts (0 on the bottom side), 20 nets.
